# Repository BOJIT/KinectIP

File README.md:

# KinectIP
NDI Streaming Tool for the Kinect V2 based on the Rock64 SBC:

Note that this repo is very unstable and not under active development! See artcile for details: [https://bojit.org/projects/KinectIP/]

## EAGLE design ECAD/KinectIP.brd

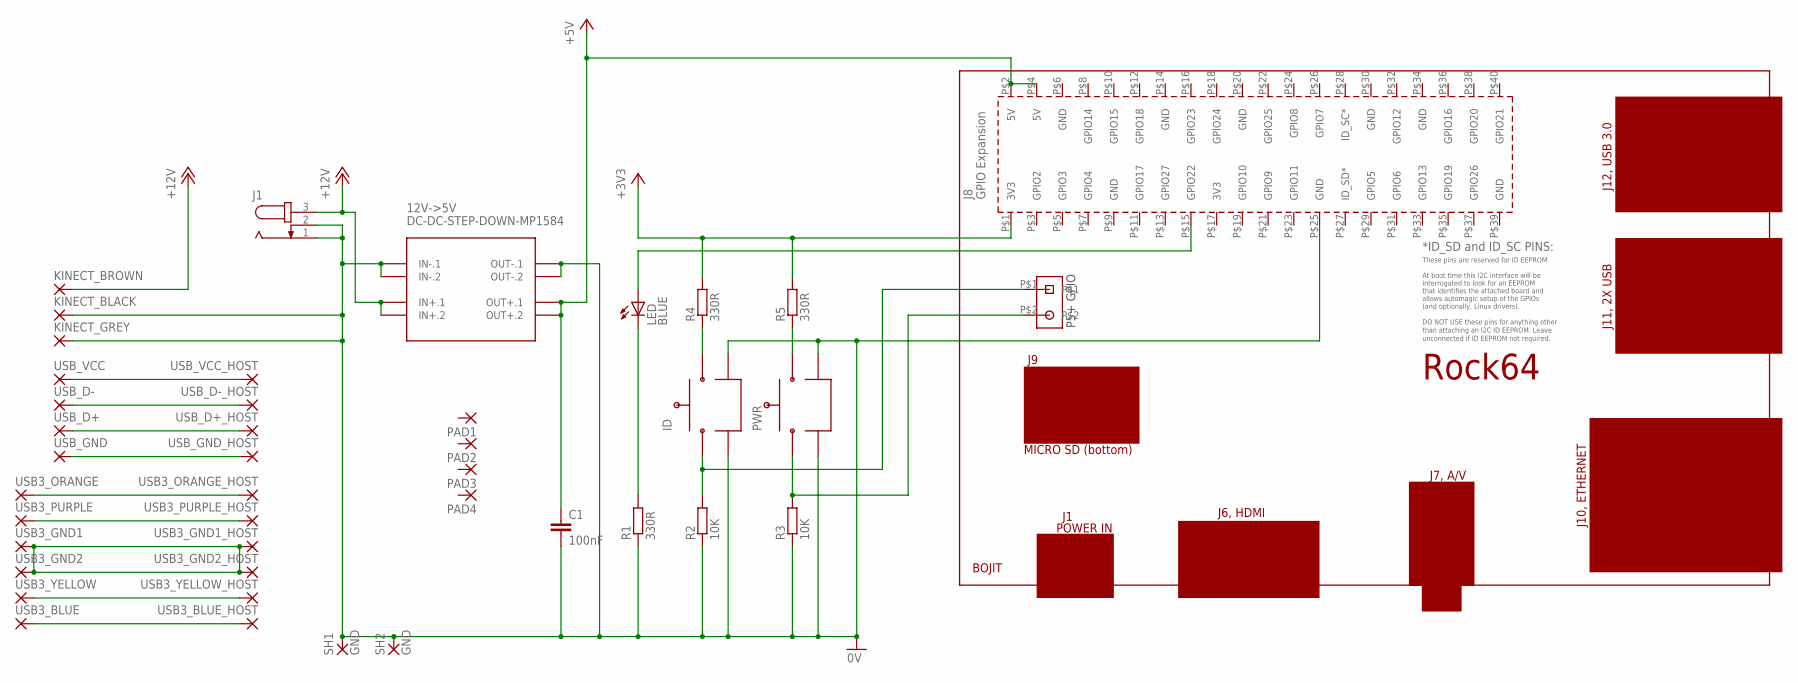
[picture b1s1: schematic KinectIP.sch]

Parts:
12V->5V: DC-DC-STEP-DOWN-MP1584
C1: 100nF; C0805K
ID: RIGHT-ANGLE-SWITCH
J1: JACK-PLUG-SLOTTED0; SPC4077
KINECT_BLACK: SMD2; SMD1,27-2,54
KINECT_BROWN: SMD2; SMD1,27-2,54
KINECT_GREY: SMD2; SMD1,27-2,54
LED: BLUE; LED-90-DEG
P5+: 2PIN-FEMALE-HEADER
PAD1, PAD2, PAD3, PAD4: 1,6/0,8
PCB2: ROCK64ROCK64; ROCK64
PWR: RIGHT-ANGLE-SWITCH
R1, R4, R5: 330R; R0805
R2, R3: 10K; R0805
SH1, SH2: GND; SMD2,54-5,08
U$1: BOJIT_COPPER; BOJIT_LARGE_COPPER
USB3_BLUE, USB3_BLUE_HOST, USB3_GND1, USB3_GND1_HOST, USB3_GND2, USB3_GND2_HOST, USB3_ORANGE, USB3_ORANGE_HOST, USB3_PURPLE, USB3_PURPLE_HOST, USB3_YELLOW, USB3_YELLOW_HOST: SMD2; SMD1,27-2,54
USB_D+: SMD2; SMD1,27-2,54
USB_D+_HOST: SMD2; SMD1,27-2,54
USB_D-: SMD2; SMD1,27-2,54
USB_D-_HOST: SMD2; SMD1,27-2,54
USB_GND: SMD2; SMD1,27-2,54
USB_GND_HOST: SMD2; SMD1,27-2,54
USB_VCC: SMD2; SMD1,27-2,54
USB_VCC_HOST: SMD2; SMD1,27-2,54

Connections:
0V: 12V->5V.IN-.1, 12V->5V.IN-.2, 12V->5V.OUT-.1, 12V->5V.OUT-.2, C1.2, ID.MNT$1, ID.MNT$2, J1.1, J1.2, KINECT_BLACK.1, KINECT_GREY.1, PCB2.P$25 (GND), PWR.MNT$1, PWR.MNT$2, R1.1, R2.1, R3.1, SH1.1, SH2.1
+3V3: PCB2.P$1 (3V3), R4.2, R5.2
+5V: 12V->5V.OUT+.1, 12V->5V.OUT+.2, C1.1, PCB2.P$2 (5V), PCB2.P$4 (5V)
+12V: 12V->5V.IN+.1, 12V->5V.IN+.2, J1.3, KINECT_BROWN.1
unnamed: LED.A, PCB2.P$15 (GPIO22)
unnamed: LED.K (C), R1.2
unnamed: ID.SW$2, R4.1
unnamed: PWR.SW$2, R5.1
unnamed: ID.SW$1, P5+.P$1, R2.2
unnamed: P5+.P$2, PWR.SW$1, R3.2
unnamed: USB_VCC.1, USB_VCC_HOST.1
unnamed: USB_D-.1, USB_D-_HOST.1
unnamed: USB_D+.1, USB_D+_HOST.1
unnamed: USB_GND.1, USB_GND_HOST.1
unnamed: USB3_ORANGE.1, USB3_ORANGE_HOST.1
unnamed: USB3_PURPLE.1, USB3_PURPLE_HOST.1
unnamed: USB3_GND1.1, USB3_GND1_HOST.1, USB3_GND2.1, USB3_GND2_HOST.1
unnamed: USB3_YELLOW.1, USB3_YELLOW_HOST.1
unnamed: USB3_BLUE.1, USB3_BLUE_HOST.1

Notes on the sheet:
P5+ GPIO

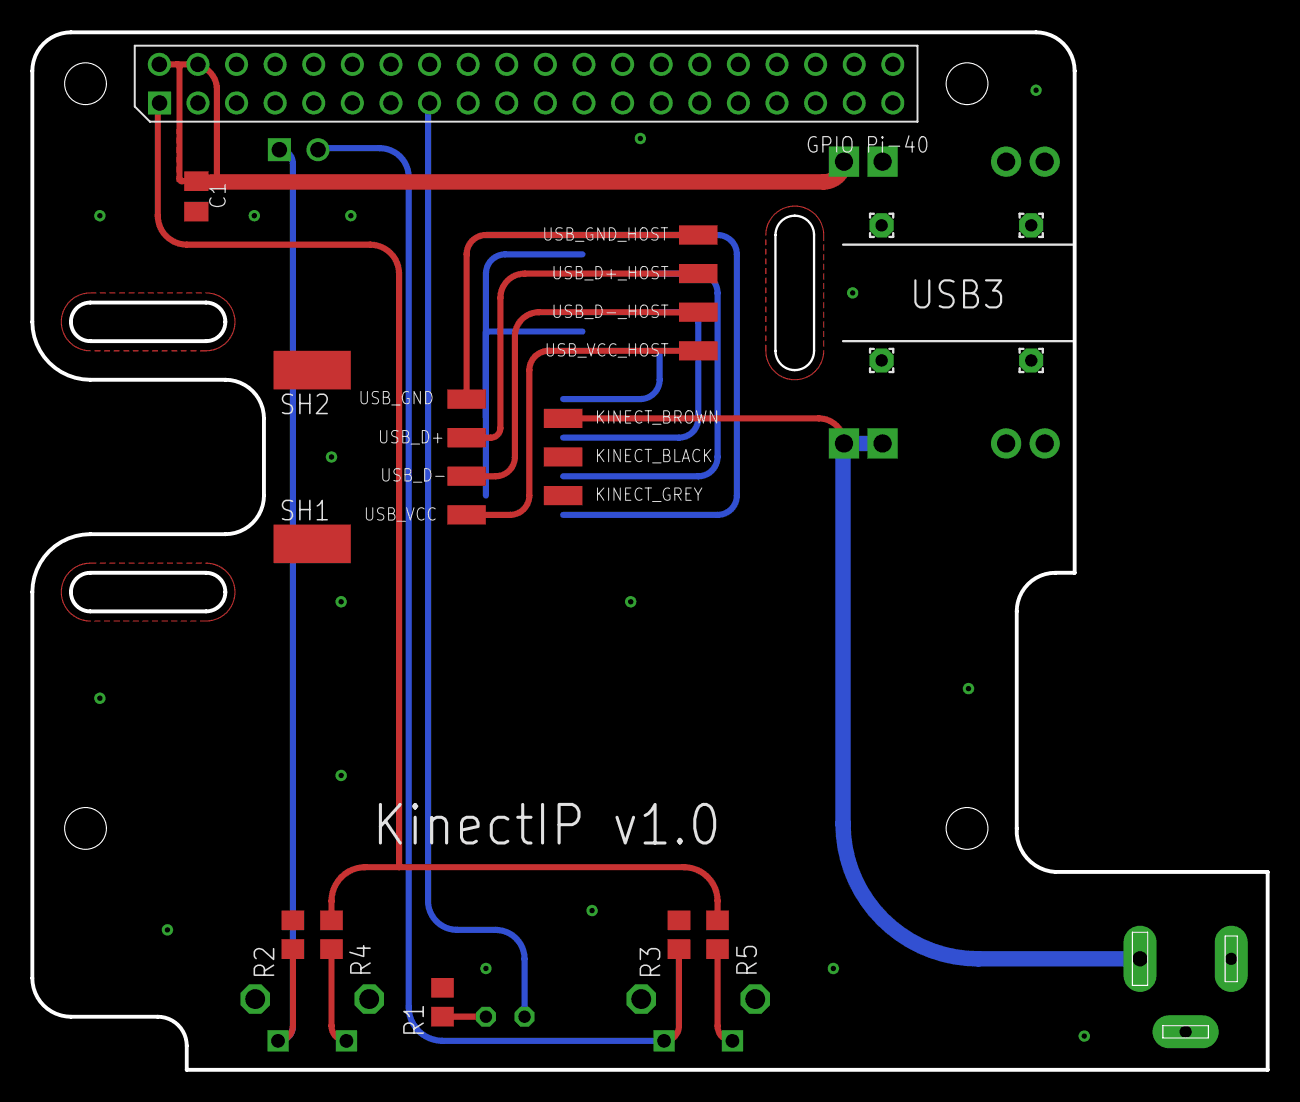
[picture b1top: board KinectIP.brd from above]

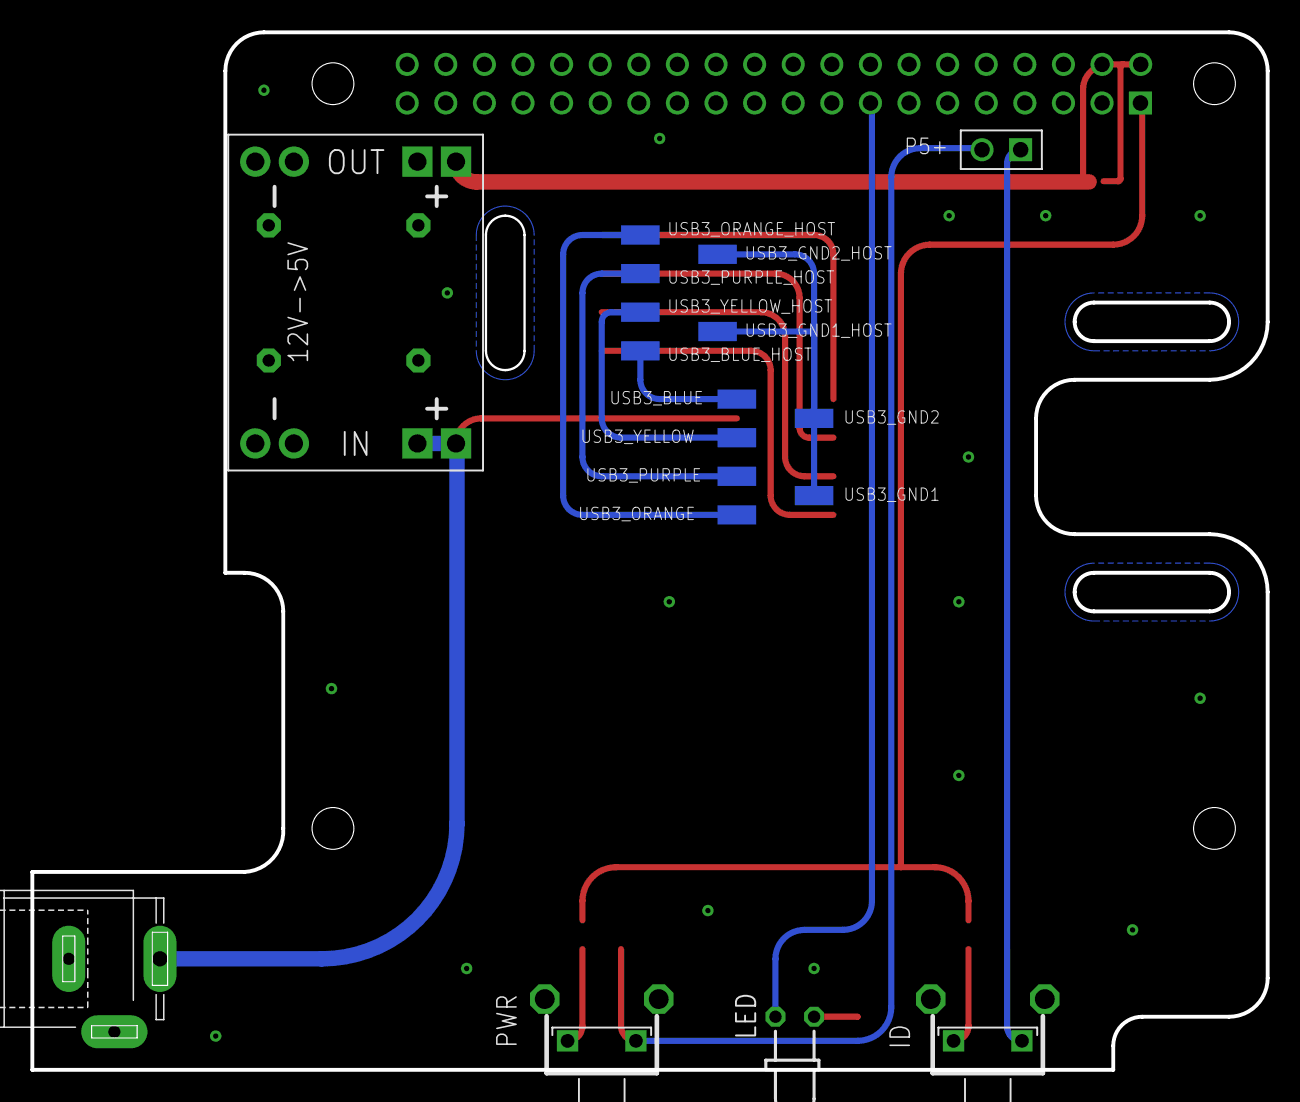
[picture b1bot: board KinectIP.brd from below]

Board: 2 copper layers, 81.3 x 68.3 mm, 43 parts (18 on the bottom side), 19 nets.

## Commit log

2019-06-13 test
2019-06-13 test dual root
2019-06-13 dev root
2019-06-13 new folder structure
2019-06-13 update scripts
2019-06-14 update libs
2019-06-14 add ndi headers
2019-06-14 fix build tasks
2019-06-14 use local sysroot
2019-06-14 dual system
2019-06-18 first successful local build
2019-06-18 mount remote filesystem
2019-06-18 sysroot
2019-06-18 it works :):):)
2019-06-18 test recompile
2019-06-19 ndi png
2019-06-19 img remove
2019-06-19 add test patterns
2019-06-19 test patterns
2019-06-19 carriage return
2019-06-20 add libfreenect
2019-06-20 link_lib
2019-06-20 Create LICENSE
2019-06-20 remove intellisense errors
2019-06-21 discover
2019-06-21 condition
2019-06-21 register kinect
2019-06-25 pointer
2019-06-25 behaving backup
2019-06-26 successful first capture
2019-06-26 correct camera format
2019-06-26 frame capture
2019-06-27 function call
2019-06-27 neat headers
2019-06-27 add config file support
2019-06-27 framerate confog
2019-06-27 kinectConfgi Problems
2019-06-28 sigint
2019-06-28 initialise frame
2019-06-28 continuous video
2019-06-28 better framerate
2019-06-28 better framerate, needs separate buffers
2019-07-22 ECAD
2019-07-22 add GPIO
2019-07-22 include
2019-07-22 gpio
2019-07-22 add c++ properties
2019-07-23 exit code
2019-07-23 remove unused variables
2019-07-23 root usr
2019-07-23 set permissions with script
2019-07-24 final direct reg
2019-07-24 bash gpio
2019-07-24 tidy
2019-07-24 pin assignments
2019-07-25 update ECAD
2019-07-25 add lbr
2019-07-25 managed lib
2019-07-25 LED Lib
2019-07-25 add MP1584
2019-07-29 ecad update
2019-07-29 fixed preprocessor stuff
2019-07-30 listener release
2019-07-30 free memory, decent framerate
2019-07-31 add deploy
2019-08-01 build webserver
2019-08-01 add netdata install
2019-08-01 netdata install
2019-08-01 complete web install
2019-08-01 build libfreenect2
2019-08-01 install libfreenect
2019-08-01 transfer
2019-08-01 full build process
2019-08-01 update log
2019-08-01 cleanup
2019-08-01 locally
2019-08-02 add shmem
2019-08-02 update SHMEM
2019-08-02 read function
2019-08-02 connection port
2019-08-02 add update_settings
2019-08-02 add return
2019-08-11 update MCAD
2023-05-22 Update link

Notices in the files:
parts and their libraries:
diy-modules: Released under the Creative Commons Attribution 4.0 International License: http://creativecommons.org/licenses/by/4.0
